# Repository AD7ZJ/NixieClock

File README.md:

# Single Tube IN-18 Nixie Clock
This is a single tube nixie clock based on a PIC16F690.  The board layout is 2 layers and easy to etch yourself if you like. 
I am building this using MPLab X and the XC8 compiler.

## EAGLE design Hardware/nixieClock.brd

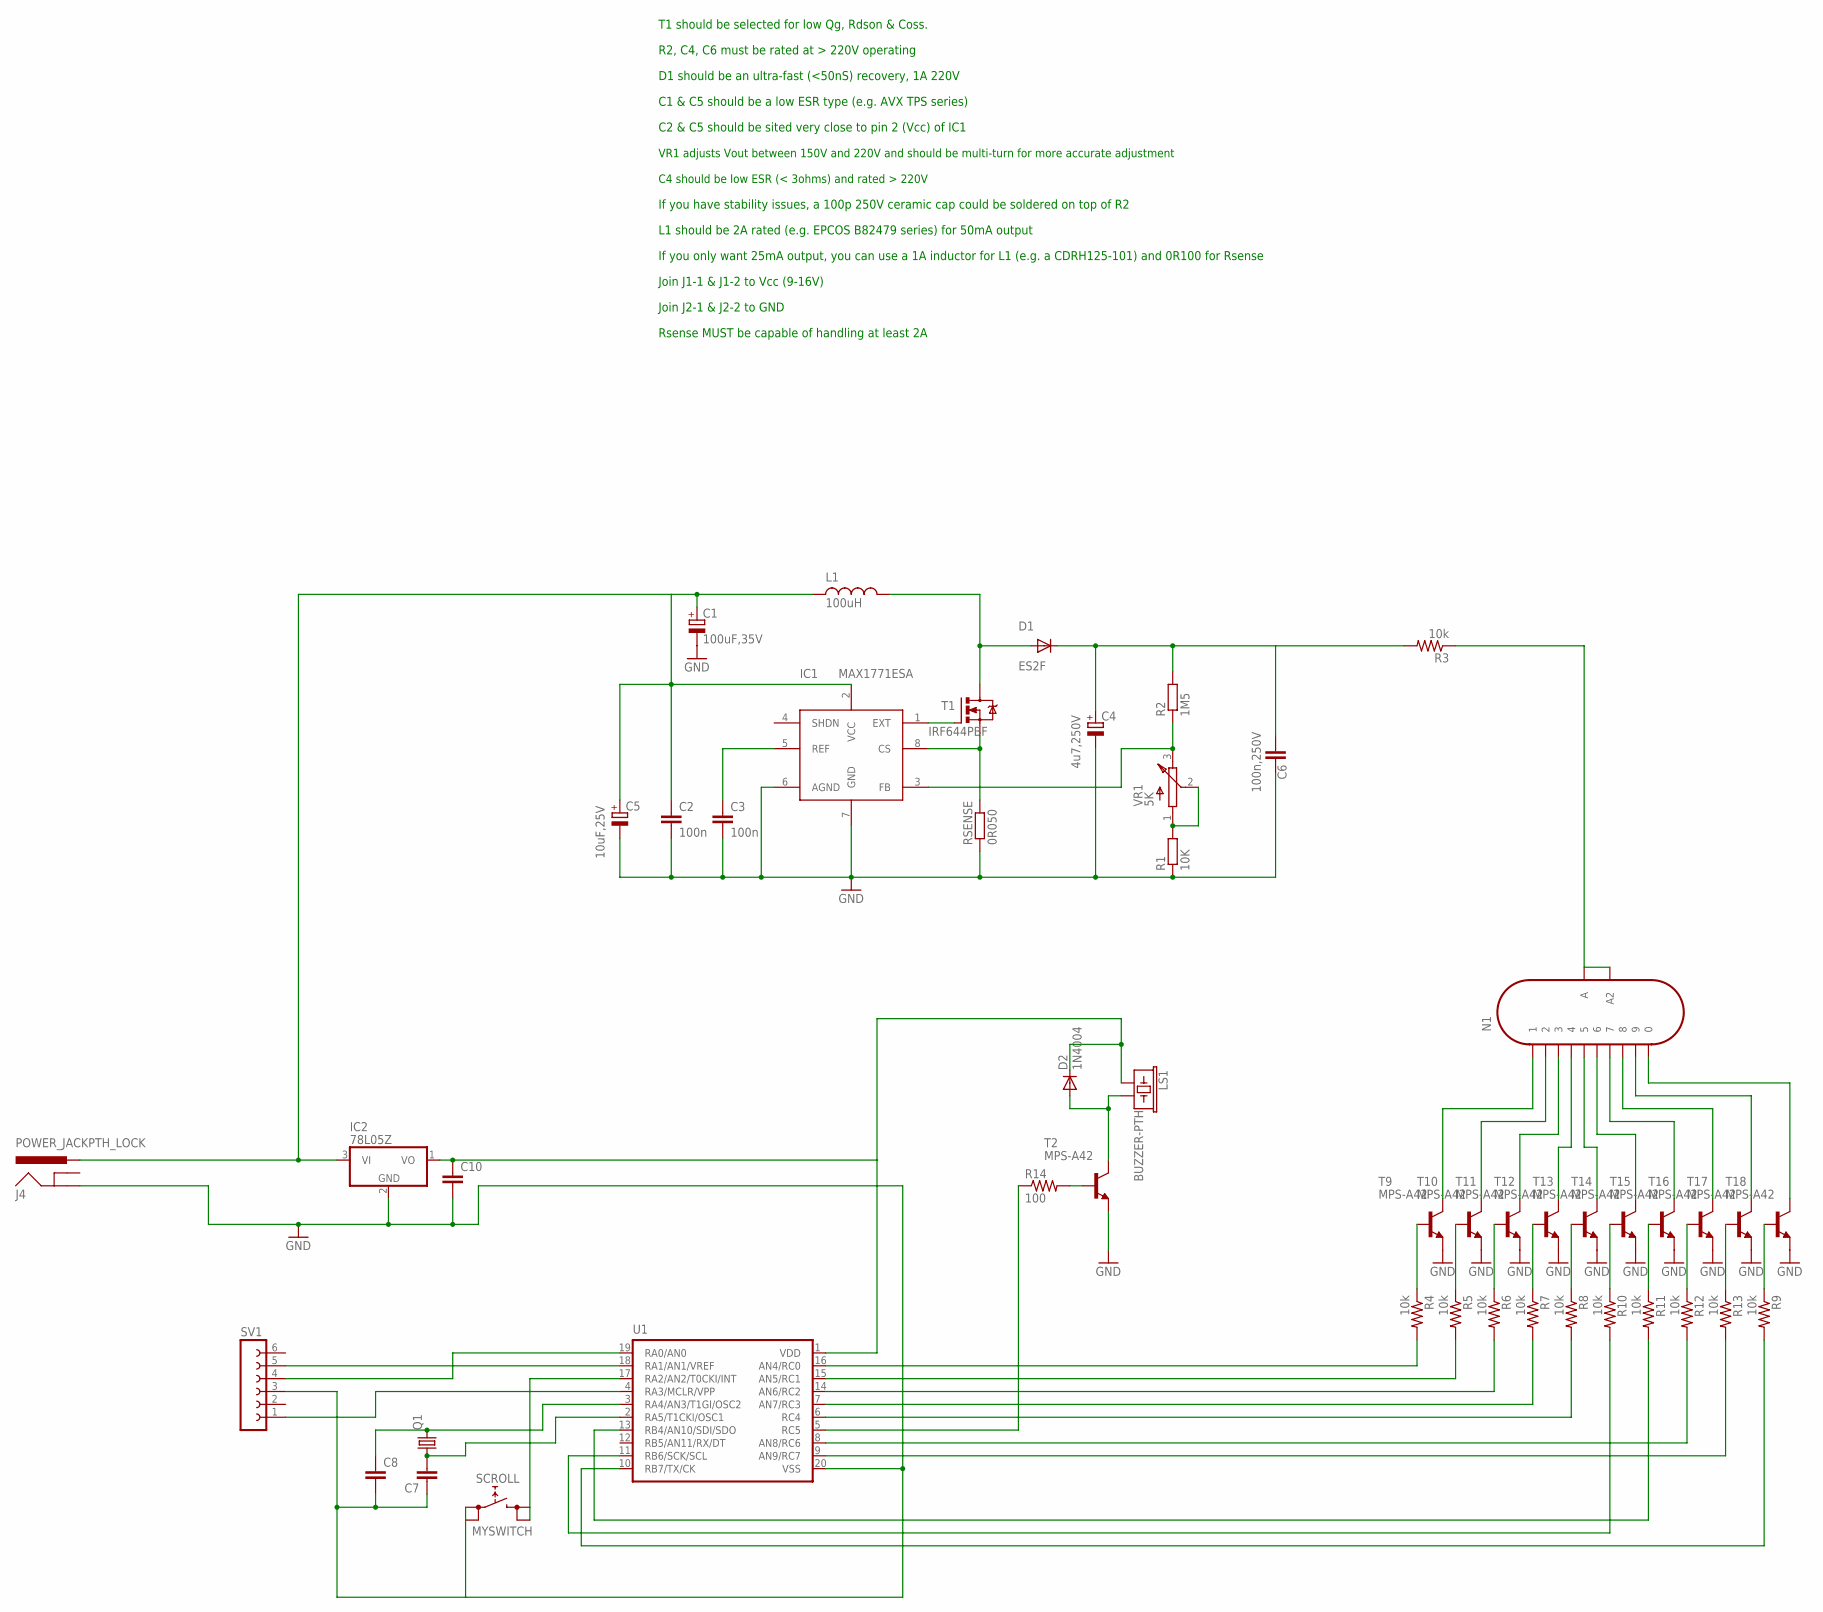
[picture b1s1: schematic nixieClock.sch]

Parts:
C1: 100uF,35V; C-EIA-7343
C2, C3: 100n; C0805
C4: 4u7,250V; NICHICON-UJ-12
C5: 10uF,25V; C-EIA-7343
C6: 100n,250V; C2420
C7, C8, C10: C2,5-3; C2.5-3
D1: ES2F; SMC
D2: 1N4004; DO41-10
IC1: MAX1771ESA; SO-8
IC2: 78L05Z; TO92
J4: POWER_JACKPTH_LOCK; POWER_JACK_PTH_LOCK
L1: 100uH; L-B82479
LS1: BUZZER-PTH; BUZZER-12MM
N1: IN-18
Q1: CRYSTALTC26V; TC26V
R1: 10K; R0805
R2: 1M5; R2512
R3, R4, R5, R6, R7, R8, R9, R10, R11, R12, R13: 10k; 0207/2V
R14: 100; 0207/2V
RSENSE: 0R050; R2010
SCROLL: MYSWITCH
SV1: FE06-1; FE06
T1: IRF644PBF; TO220BV
T2, T9, T10, T11, T12, T13, T14, T15, T16, T17, T18: MPS-A42; TO92-CBE
U1: PIC16F6XX; DIL20
VR1: 5K; BOURNS-3214W

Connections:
EXT: IC1.1 (EXT), T1.G
GND: C1.-, C2.2, C3.2, C4.1 (-), C5.-, C6.P$2 (2), C7.1, C8.2, C10.2, IC1.6 (AGND), IC1.7 (GND), IC2.2 (GND), J4.GND, R1.1, RSENSE.1, SCROLL.A0 (0), SCROLL.A1 (0), SV1.3, T2.E, T9.E, T10.E, T11.E, T12.E, T13.E, T14.E, T15.E, T16.E, T17.E, T18.E, U1.20 (VSS)
unnamed: N1.1, T9.C
unnamed: IC1.8 (CS), RSENSE.2, T1.S
unnamed: R1.2, VR1.1 (A), VR1.2 (W)
unnamed: SV1.1, U1.4 (RA3/MCLR/VPP)
unnamed: R8.2, U1.6 (RC4)
unnamed: R4.1, T9.B
unnamed: IC1.3 (FB), R2.1, VR1.3 (B)
unnamed: R5.1, T10.B
unnamed: R4.2, U1.16 (AN4/RC0)
unnamed: R5.2, U1.15 (AN5/RC1)
unnamed: R6.2, U1.14 (AN6/RC2)
unnamed: R7.2, U1.7 (AN7/RC3)
unnamed: SV1.4, U1.19 (RA0/AN0)
unnamed: D1.A, L1.P$2 (2), T1.D
unnamed: SV1.5, U1.18 (RA1/AN1/VREF)
unnamed: C3.1, IC1.5 (REF)
unnamed: R14.1, U1.5 (RC5)
unnamed: R12.2, U1.8 (AN8/RC6)
unnamed: R6.1, T11.B
unnamed: R13.2, U1.9 (AN9/RC7)
unnamed: R7.1, T12.B
unnamed: R8.1, T13.B
unnamed: C7.2, Q1.1, U1.2 (RA5/T1CKI/OSC1)
unnamed: R10.1, T14.B
unnamed: C8.1, Q1.2, U1.3 (RA4/AN3/T1GI/OSC2)
unnamed: R11.1, T15.B
unnamed: R12.1, T16.B
unnamed: R13.1, T17.B
unnamed: C10.1, D2.C, IC2.1 (VO), LS1.+ (1), U1.1 (VDD)
unnamed: R9.1, T18.B
unnamed: R10.2, U1.11 (RB6/SCK/SCL)
unnamed: R9.2, U1.10 (RB7/TX/CK)
unnamed: SCROLL.B0 (1), SCROLL.B1 (1), U1.17 (RA2/AN2/T0CKI/INT)
unnamed: N1.2, T10.C
unnamed: R11.2, U1.13 (RB4/AN10/SDI/SDO)
unnamed: D2.A, LS1.- (2), T2.C
unnamed: R14.2, T2.B
unnamed: N1.3, T11.C
unnamed: N1.4, T12.C
unnamed: N1.5, T13.C
unnamed: N1.6, T14.C
unnamed: N1.7, T15.C
unnamed: N1.8, T16.C
unnamed: N1.9, T17.C
unnamed: N1.0, T18.C
unnamed: N1.A, N1.A2, R3.1
PWR: C1.+, C2.1, C5.+, IC1.2 (VCC), IC2.3 (VI), J4.PWR, L1.P$1 (1)
VOUT: C4.2 (+), C6.P$1 (1), D1.C, R2.2, R3.2

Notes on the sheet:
R2, C4, C6 must be rated at > 220V operating
D1 should be an ultra-fast (<50nS) recovery, 1A 220V
C1 & C5 should be a low ESR type (e.g. AVX TPS series)
C2 & C5 should be sited very close to pin 2 (Vcc) of IC1
VR1 adjusts Vout between 150V and 220V and should be multi-turn for more accurate adjustment
C4 should be low ESR (< 3ohms) and rated > 220V
If you have stability issues, a 100p 250V ceramic cap could be soldered on top of R2
L1 should be 2A rated (e.g. EPCOS B82479 series) for 50mA output
Join J1-1 & J1-2 to Vcc (9-16V)
Join J2-1 & J2-2 to GND
T1 should be selected for low Qg, Rdson & Coss.
Rsense MUST be capable of handling at least 2A
If you only want 25mA output, you can use a 1A inductor for L1 (e.g. a CDRH125-101) and 0R100 for Rsense

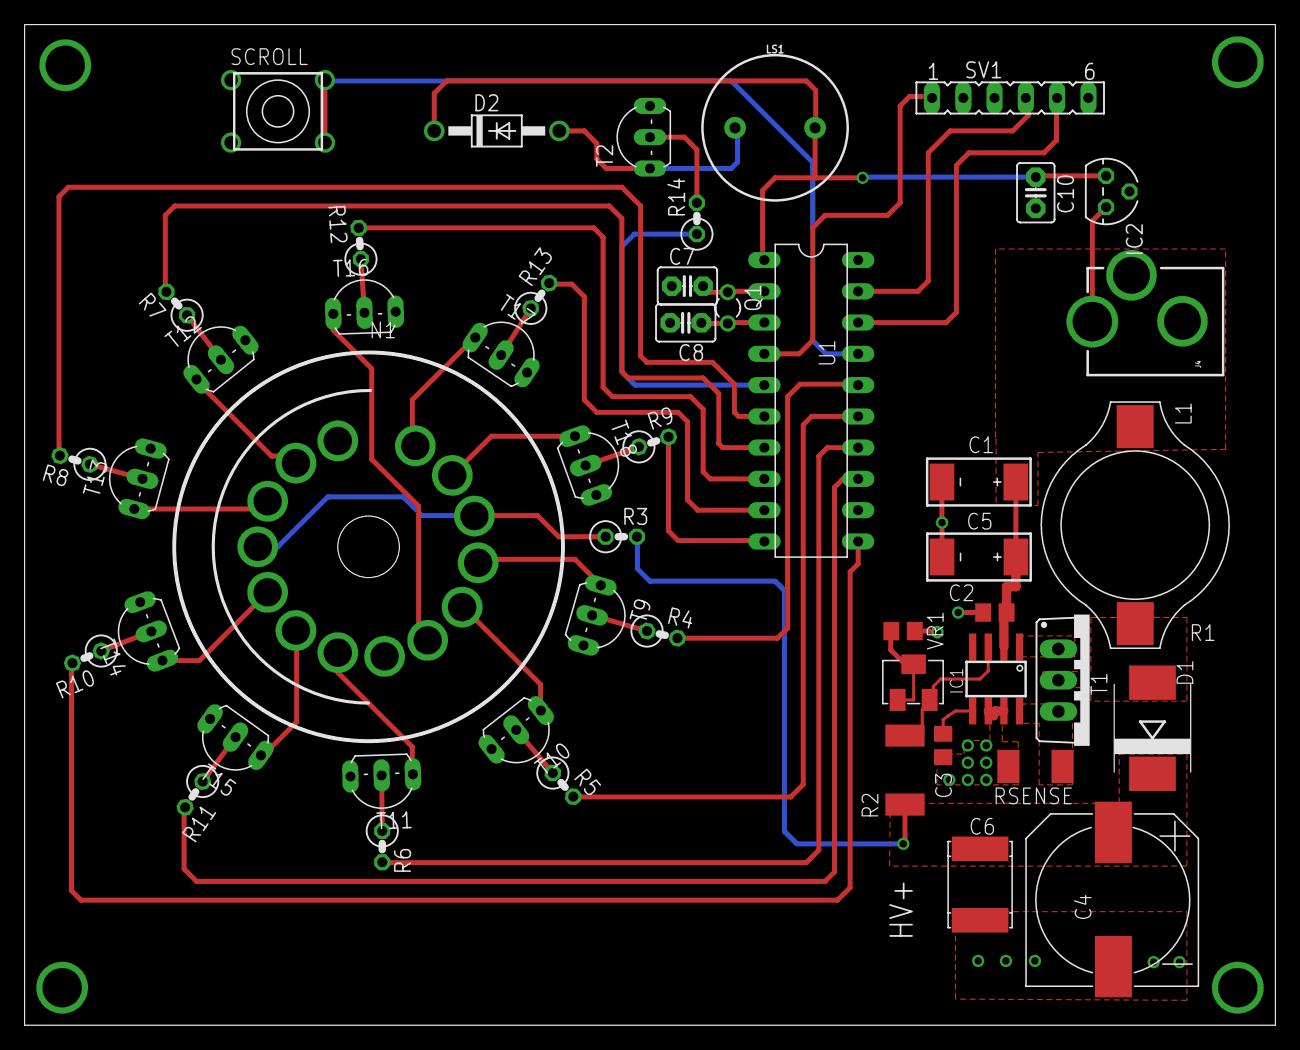
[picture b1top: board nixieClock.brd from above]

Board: 2 copper layers, 101.6 x 81.3 mm, 49 parts (0 on the bottom side), 50 nets.

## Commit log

2017-02-04 Check in initial schematic and board layout
2017-02-18 Added software
2026-01-09 Rework for latest XC8. First cut at adding cal routine.
2026-01-09 Add off time to setcal routine.

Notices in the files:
parts and their libraries:
SparkFun-Connectors: Licensing: Creative Commons ShareAlike 4.0 International - https://creativecommons.org/licenses/by-sa/4.0
